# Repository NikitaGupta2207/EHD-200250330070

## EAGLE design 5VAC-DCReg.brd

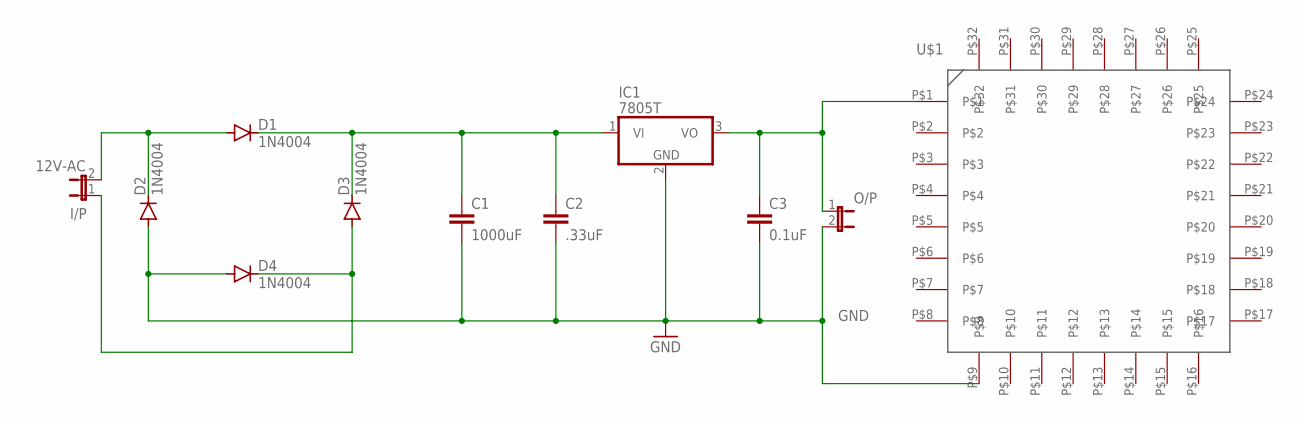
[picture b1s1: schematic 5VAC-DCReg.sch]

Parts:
C1: 1000uF; C2.5-3
C2: .33uF; C2.5-3
C3: 0.1uF; C2.5-3
D1, D2, D3, D4: 1N4004; DO41-10
I/P: 12V-AC; JP1
IC1: 7805T; TO220H
O/P: JP1E; JP1
U$1: MEGA8L-DEV; TQFP-MEGA8L

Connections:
GND: C1.2, C2.2, C3.2, D2.A, D4.A, IC1.2 (GND), O/P.2, U$1.P$9
unnamed: D1.A, D2.C, I/P.2
unnamed: D3.A, D4.C, I/P.1
unnamed: C1.1, C2.1, D1.C, D3.C, IC1.1 (VI)
unnamed: C3.1, IC1.3 (VO), O/P.1, U$1.P$1

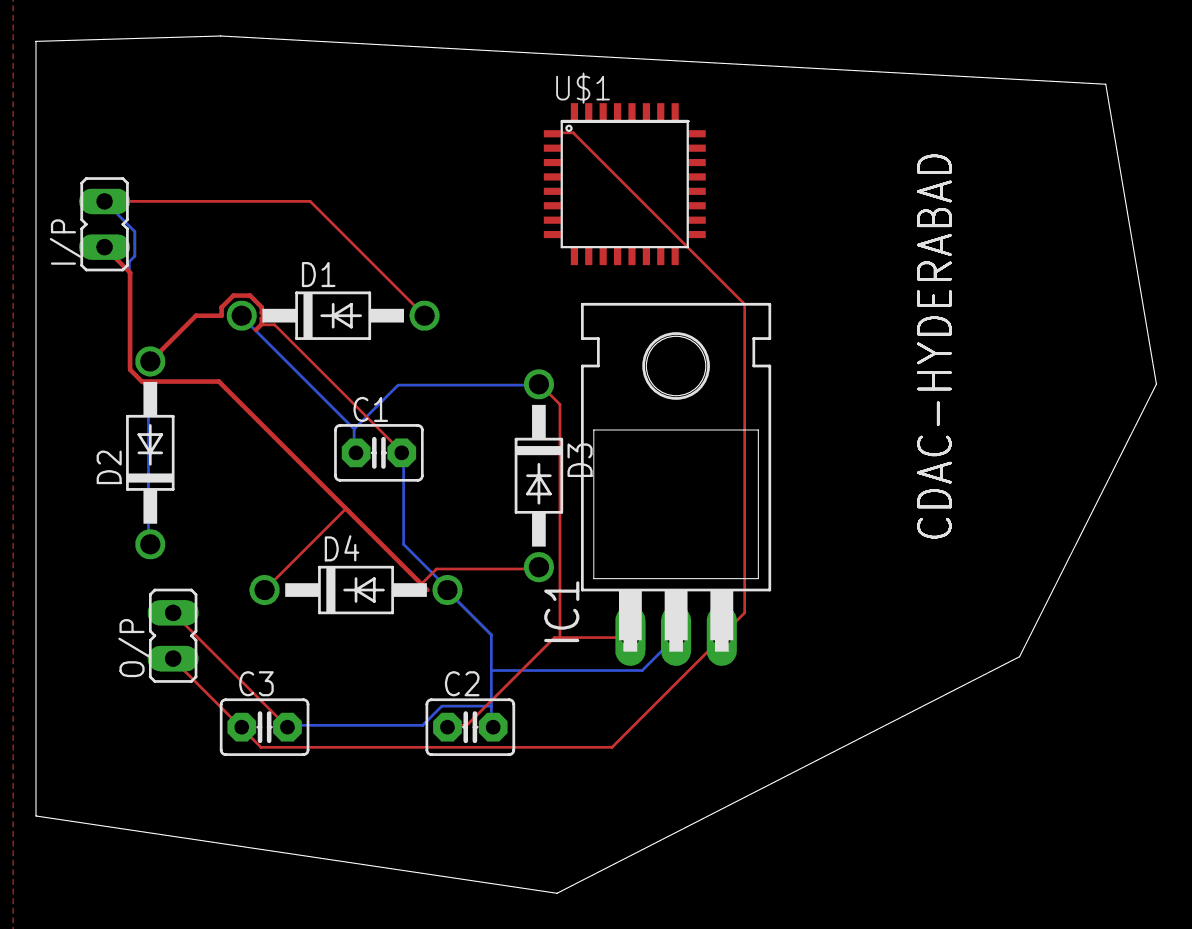
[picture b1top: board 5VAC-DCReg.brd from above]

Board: 2 copper layers, 62.2 x 47.6 mm, 11 parts (0 on the bottom side), 5 nets.

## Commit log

2020-10-17 Add files via upload
    I/O Board (Top) for MultiBot
